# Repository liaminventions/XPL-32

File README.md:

# XPL-32

The XPL-32 is a homebrew 8-bit 6502 laptop, with four 48-pin expansion slots, and a 22-pin I/O port.
 ### XPL-32 stands for:
e**X**pandable 
**P**ersonal 
**L**aptop 
with **32**k ram
# [Blog](https://unstinkableinventions.wordpress.com/)
Here I will post hardware updates to the XPL and more.

Also, be sure to check info.txt to know if there are any issues when i code.
# Hardware Overview
## CPU
A 6502, of course. A W65C02 to be exact. 

[Datasheet](https://eater.net/datasheets/w65c02s.pdf)
## I/O
For the I/O, I've got a W65C22 VIA. Port A, Port B and the handshake bits connect to the I/O slot.
However CA2 is connected to the Video Switch Relay (VSR)
[W65C22 Datasheet](https://eater.net/datasheets/w65c22.pdf)
## Video
The XPL-32 has an expandable monochrome terminal display that uses a 6551 ACIA  at $8000 and two arduinos.
[This is the video and keyboard processer. (not made by me)](http://searle.x10host.com/MonitorKeyboard/index.html)
The video can be switched to the composite input EXTVID (on the expansion port) by toggling the VSR. (a relay that switches beetween native video and EXTVID.)

So far, for Video expansions, I've made a TMS9918a one. (the same video processer used in the TI-99/4a and the MSX)
## Sound
There is a 6581 SID at $B800 ($D400 in the c64) onboard with its potentiometer (POTX and POTY) and external sound (EXTSND) inputs on the expansion port.
I programmed support to convert most SID files, as well.
# Memory Map

# Tools I Use
## PCB Design
I currently use [EAGLE](https://www.autodesk.com/products/eagle/free-download)
## 3D Modeling
[Fusion 360](https://www.autodesk.com/products/fusion-360/overview?us_oa=dotcom-us&us_si=4e5471dc-07ed-4416-80c0-6f3e9f7c15b4&us_pt=NINVFUS&us_at=%5Bobject%20Object%5D&term=1-YEAR&tab=subscription&plc=F360)
## Coding
[VIM](https://www.vim.org/), [NVIM](https://neovim.io/)/[LunarVIM](https://www.lunarvim.org/) or [vscode](https://code.visualstudio.com/) for code editing.
[xa](https://github.com/fachat/xa65), [ca65](https://github.com/cc65/cc65) (from cc65), and [vasm](http://sun.hasenbraten.de/vasm/) for assembly.

I have "xa 6502 cross assembler" syntax highlighting in vim, and the "vasm" extension in vscode.

most source files are .s, but some are .a65 or .asm

## Debugging 

I use [Pulseview](https://sigrok.org/wiki/PulseView) with [this logic analyzer (the 2018 variant)](https://sigrok.org/wiki/Mcupro_Logic16_clone)

It was an absolute pain to set up...

Also, the SDcard-SPI decoder in libsigrokdecode was completly broken for me. (it always expected a CRC...) My fix was to make [my own custom version of the decoder](https://github.com/liaminventions/XPL-32/tree/main/debug/decoders/sdcard_spi)

The custom version is still slightly broken, but I am working on it.

I also use [decode6502 by hoglet](https://github.com/hoglet67/6502Decoder)

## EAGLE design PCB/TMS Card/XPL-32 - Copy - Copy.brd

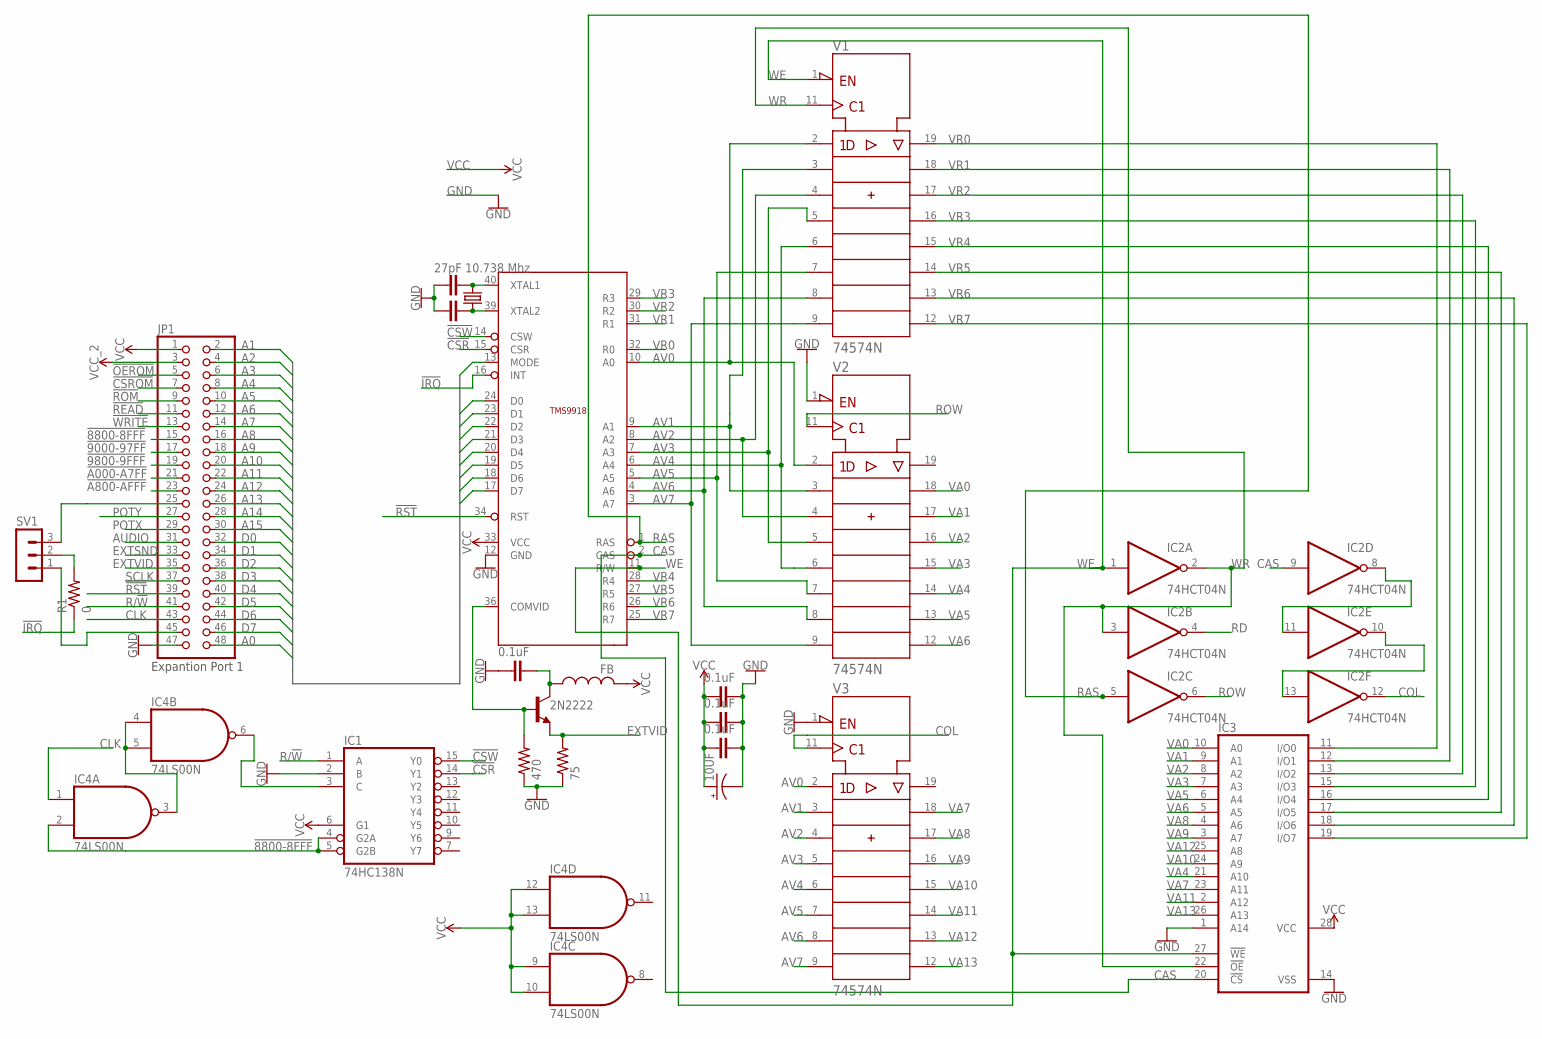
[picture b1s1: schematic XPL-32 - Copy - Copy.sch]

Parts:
10.738MHZ: CRYSTALS-NOGND-HC49; HC49
10UF: CPOL-USE2.5-7; E2,5-7
30PF, 30PF(2): C-EU025-030X050; C025-030X050
C1, C2, C3, C6: 0.1uF; C025-025X050
IC1: 74HC138N; DIL16
IC2: 74HCT04N; DIL14
IC3: 62256P; DIL28-6
IC4: 74LS00N; DIL14
JP1: PINHD-2X24/90; 2X24/90
R1: 0; 0204/7
R9: 470; 0204/7
R10: 75; 0204/7
SV1: MA03-1
T2: 2N2222; TO92-EBC-OVAL
U$4: FB
V1, V2, V3: 74574N; DIL20
VDP: TMS9918; DIP-40

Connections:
!8800-8FFF: IC1.4 (G2A), IC1.5 (G2B), IC4.2 (I1), JP1.15
!9000-97FF: JP1.17
!9800-9FFF: JP1.19
!A000-A7FF: JP1.21
!A800-AFFF: JP1.23
!CSR: IC1.14 (Y1), VDP.15 (CSR)
!CSROM: JP1.7
!CSW: IC1.15 (Y0), VDP.14 (CSW)
!IRQ: R1.1, VDP.16 (INT)
!OEROM: JP1.5
!READ: JP1.11
!ROM: JP1.9
!RST: JP1.39, VDP.34 (RST)
!WRITE: JP1.13
A0: JP1.48, VDP.13 (MODE)
A1: JP1.2
A2: JP1.4
A3: JP1.6
A4: JP1.8
A5: JP1.10
A6: JP1.12
A7: JP1.14
A8: JP1.16
A9: JP1.18
A10: JP1.20
A11: JP1.22
A12: JP1.24
A13: JP1.26
A14: JP1.28
A15: JP1.30
AUDIO: JP1.31
AV0: V1.2 (1D), V2.2 (1D), V3.2 (1D), VDP.10 (A0)
AV1: V1.3 (2D), V2.3 (2D), V3.3 (2D), VDP.9 (A1)
AV2: V1.4 (3D), V2.4 (3D), V3.4 (3D), VDP.8 (A2)
AV3: V1.5 (4D), V2.5 (4D), V3.5 (4D), VDP.7 (A3)
AV4: V1.6 (5D), V2.6 (5D), V3.6 (5D), VDP.6 (A4)
AV5: V1.7 (6D), V2.7 (6D), V3.7 (6D), VDP.5 (A5)
AV6: V1.8 (7D), V2.8 (7D), V3.8 (7D), VDP.4 (A6)
AV7: V1.9 (8D), V2.9 (8D), V3.9 (8D), VDP.3 (A7)
CAS: IC2.9 (I), IC3.20 (!CS), VDP.2 (CAS)
CLK: IC4.1 (I0), JP1.43
COL: IC2.12 (O), V3.11 (CLK)
D0: JP1.32, VDP.17 (D7)
D1: JP1.34, VDP.18 (D6)
D2: JP1.36, VDP.19 (D5)
D3: JP1.38, VDP.20 (D4)
D4: JP1.40, VDP.21 (D3)
D5: JP1.42, VDP.22 (D2)
D6: JP1.44, VDP.23 (D1)
D7: JP1.46, VDP.24 (D0)
EXTSND: JP1.33
EXTVID: JP1.35, R10.2, T2.E
GND: 10UF.-, 30PF.1, 30PF(2).1, C1.2, C2.2, C3.2, C6.1, IC1.2 (B), IC1.8 (GND), IC2.7 (GND), IC3.1 (A14), IC3.14 (VSS), IC4.7 (GND), JP1.47, R9.1, R10.1, V1.10 (-UB), V2.1 (!OC), V2.10 (-UB), V3.1 (!OC), V3.10 (-UB), VDP.12 (GND)
unnamed: IC1.3 (C), IC4.6 (O)
unnamed: JP1.45, SV1.1
unnamed: IC2.8 (O), IC2.11 (I)
unnamed: IC2.10 (O), IC2.13 (I)
unnamed: JP1.25, SV1.3
unnamed: R1.2, SV1.2
unnamed: IC4.3 (O), IC4.4 (I0), IC4.5 (I1)
unnamed: C6.2, T2.C, U$4.P$1 (1)
unnamed: R9.2, T2.B, VDP.36 (COMVID)
unnamed: 10.738MHZ.1, 30PF.2, VDP.40 (XTAL1)
unnamed: 10.738MHZ.2, 30PF(2).2, VDP.39 (XTAL2)
POTX: JP1.29
POTY: JP1.27
R/!W: IC1.1 (A), JP1.41
RAS: IC2.5 (I), VDP.1 (RAS)
RD: IC2.4 (O)
ROW: IC2.6 (O), V2.11 (CLK)
SCLK: JP1.37
VA0: IC3.10 (A0), V2.18 (2Q)
VA1: IC3.9 (A1), V2.17 (3Q)
VA2: IC3.8 (A2), V2.16 (4Q)
VA3: IC3.7 (A3), V2.15 (5Q)
VA4: IC3.21 (A10), V2.14 (6Q)
VA5: IC3.6 (A4), V2.13 (7Q)
VA6: IC3.5 (A5), V2.12 (8Q)
VA7: IC3.23 (A11), V3.18 (2Q)
VA8: IC3.4 (A6), V3.17 (3Q)
VA9: IC3.3 (A7), V3.16 (4Q)
VA10: IC3.24 (A9), V3.15 (5Q)
VA11: IC3.2 (A12), V3.14 (6Q)
VA12: IC3.25 (A8), V3.13 (7Q)
VA13: IC3.26 (A13), V3.12 (8Q)
VCC: 10UF.+, C1.1, C2.1, C3.1, IC1.6 (G1), IC1.16 (VCC), IC2.14 (VCC), IC3.28 (VCC), IC4.9 (I0), IC4.10 (I1), IC4.12 (I0), IC4.13 (I1), IC4.14 (VCC), JP1.1, U$4.P$2 (2), V1.20 (+UB), V2.20 (+UB), V3.20 (+UB), VDP.33 (VCC)
VCC_2: JP1.3
VR0: IC3.11 (I/O0), V1.19 (1Q), VDP.32 (R0)
VR1: IC3.12 (I/O1), V1.18 (2Q), VDP.31 (R1)
VR2: IC3.13 (I/O2), V1.17 (3Q), VDP.30 (R2)
VR3: IC3.15 (I/O3), V1.16 (4Q), VDP.29 (R3)
VR4: IC3.16 (I/O4), V1.15 (5Q), VDP.28 (R4)
VR5: IC3.17 (I/O5), V1.14 (6Q), VDP.27 (R5)
VR6: IC3.18 (I/O6), V1.13 (7Q), VDP.26 (R6)
VR7: IC3.19 (I/O7), V1.12 (8Q), VDP.25 (R7)
WE: IC2.1 (I), IC3.27 (!WE), V1.1 (!OC), VDP.11 (R/W)
WR: IC2.2 (O), IC2.3 (I), IC3.22 (!OE), V1.11 (CLK)

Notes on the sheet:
Expantion Port 1
27pF 10.738 Mhz

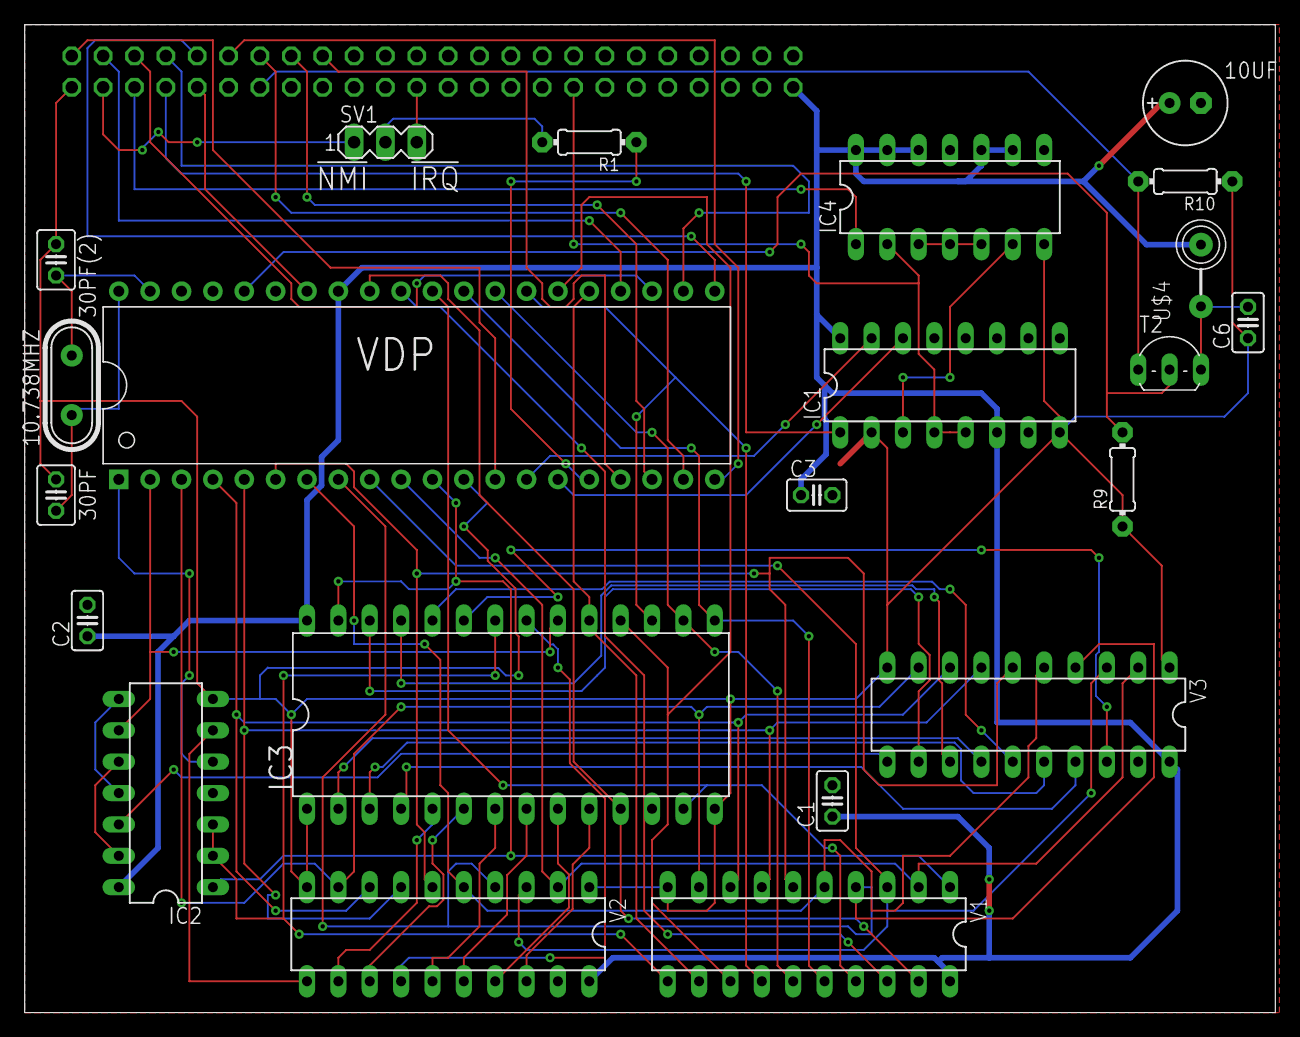
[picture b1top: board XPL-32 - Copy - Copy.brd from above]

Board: 2 copper layers, 101.3 x 80.0 mm, 23 parts (1 on the bottom side), 66 nets.

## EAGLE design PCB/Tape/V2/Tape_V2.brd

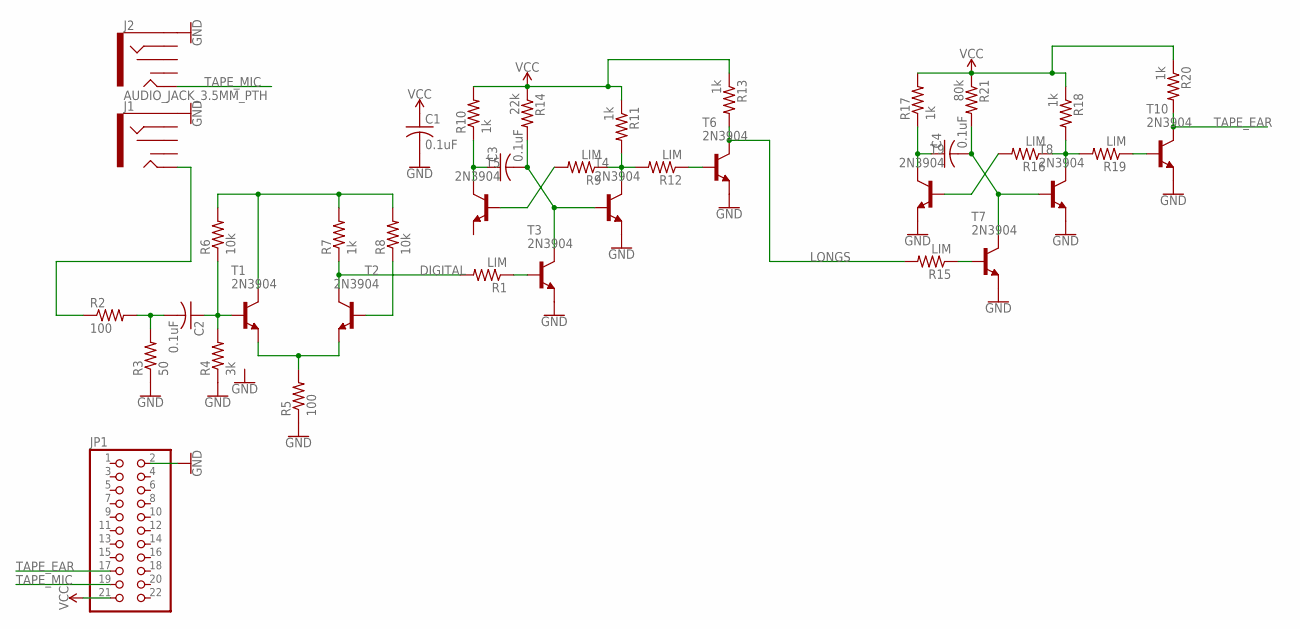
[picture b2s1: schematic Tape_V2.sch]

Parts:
C1, C2, C3, C4: 0.1uF; C025-030X050
J1, J2: AUDIO_JACK_3.5MM_PTH; AUDIO-JACK
JP1: PINHD-2X11/90; 2X11/90
R1, R9, R12, R15, R16, R19: LIM; 0204/7
R2, R5: 100; 0204/7
R3: 50; 0204/7
R4: 3k; 0204/7
R6, R8: 10k; 0204/7
R7, R10, R11, R13, R17, R18, R20: 1k; 0204/7
R14: 22k; 0204/7
R21: 80k; 0204/7
T1, T2, T3, T4, T5, T6, T7, T8, T9, T10: 2N3904; TO92

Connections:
DIGITAL: R1.2, R7.1, T2.1 (C)
GND: C1.2, J1.SLEEVE, J2.SLEEVE, JP1.2, R3.1, R4.1, R5.1, T3.3 (E), T4.3 (E), T6.3 (E), T7.3 (E), T8.3 (E), T9.3 (E), T10.3 (E); also elsewhere on the board
LONGS: R13.2, R15.2, T6.1 (C)
unnamed: R5.2, T1.3 (E), T2.3 (E)
unnamed: C2.1, R4.2, R6.1, T1.2 (B)
unnamed: C2.2, R2.2, R3.2
unnamed: R6.2, R7.2, R8.2, T1.1 (C)
unnamed: R1.1, T3.2 (B)
unnamed 8: R8.1, T2.2 (B); also elsewhere on the board
unnamed: J1.TIP, R2.1
unnamed: C3.2, R14.2, T3.1 (C), T4.2 (B)
unnamed: R9.2, T5.2 (B)
unnamed: C3.1, R10.1, T5.1 (C)
unnamed: R9.1, R11.2, R12.2, T4.1 (C)
unnamed: R12.1, T6.2 (B)
unnamed: R15.1, T7.2 (B)
unnamed: C4.2, R21.2, T7.1 (C), T8.2 (B)
unnamed: R16.2, T9.2 (B)
unnamed: C4.1, R17.1, T9.1 (C)
unnamed: R16.1, R18.2, R19.2, T8.1 (C)
unnamed: R19.1, T10.2 (B)
TAPE_EAR: JP1.17, R20.2, T10.1 (C)
TAPE_MIC: J2.TIP, JP1.19
VCC: C1.1, JP1.21, R10.2, R11.1, R13.1, R14.1, R17.2, R18.1, R20.1, R21.1

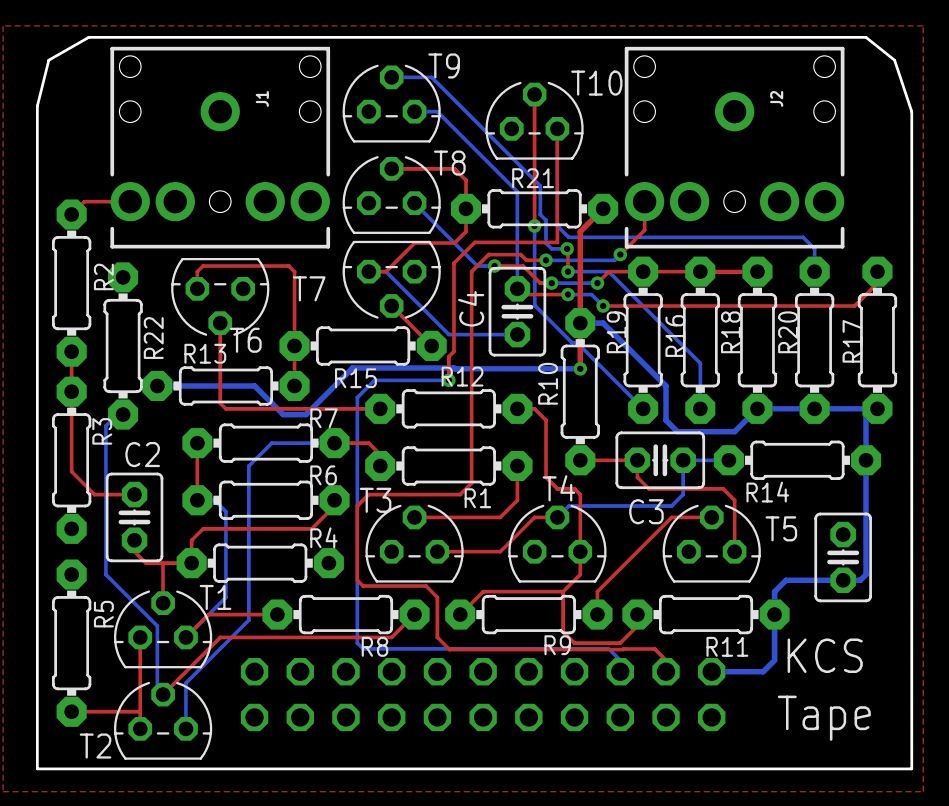
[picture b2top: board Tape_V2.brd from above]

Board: 2 copper layers, 48.6 x 40.6 mm, 39 parts (1 on the bottom side), 24 nets.

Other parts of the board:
R22: 3k; 0204/7

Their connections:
GND: R22.1; also elsewhere on the board
unnamed 8: R22.2; also elsewhere on the board

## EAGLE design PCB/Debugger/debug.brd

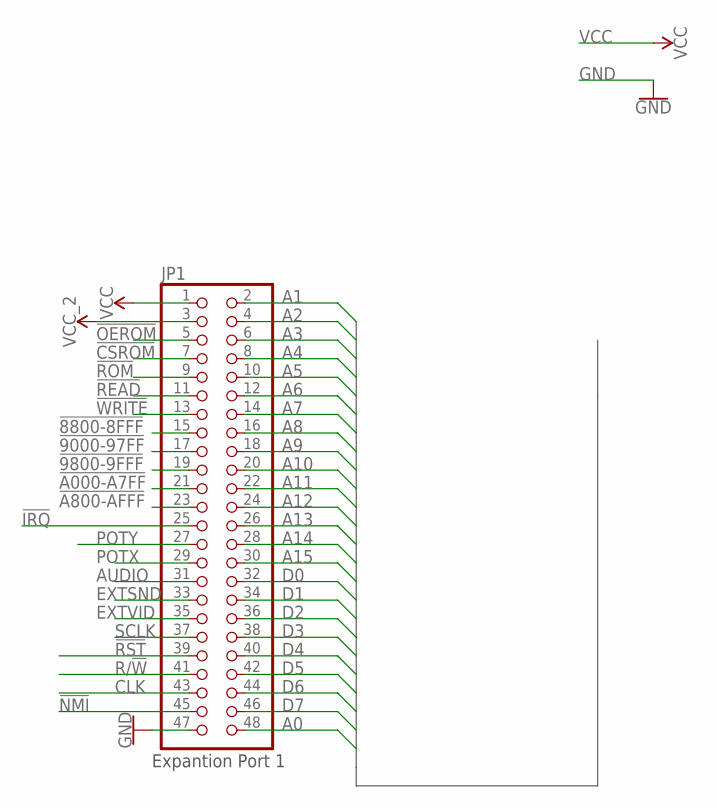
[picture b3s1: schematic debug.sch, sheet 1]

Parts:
JP1: PINHD-2X24/90; 2X24/90

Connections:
!8800-8FFF: JP1.15
!9000-97FF: JP1.17
!9800-9FFF: JP1.19
!A000-A7FF: JP1.21
!A800-AFFF: JP1.23
!CSROM: JP1.7
!IRQ: JP1.25; also elsewhere on the board
!NMI: JP1.45; also elsewhere on the board
!OEROM: JP1.5
!READ: JP1.11
!ROM: JP1.9
!RST: JP1.39
!WRITE: JP1.13
A0: JP1.48; also elsewhere on the board
A1: JP1.2; also elsewhere on the board
A2: JP1.4; also elsewhere on the board
A3: JP1.6; also elsewhere on the board
A4: JP1.8; also elsewhere on the board
A5: JP1.10; also elsewhere on the board
A6: JP1.12; also elsewhere on the board
A7: JP1.14; also elsewhere on the board
A8: JP1.16; also elsewhere on the board
A9: JP1.18; also elsewhere on the board
A10: JP1.20; also elsewhere on the board
A11: JP1.22; also elsewhere on the board
A12: JP1.24; also elsewhere on the board
A13: JP1.26; also elsewhere on the board
A14: JP1.28; also elsewhere on the board
A15: JP1.30; also elsewhere on the board
AUDIO: JP1.31
CLK: JP1.43; also elsewhere on the board
D0: JP1.32; also elsewhere on the board
D1: JP1.34; also elsewhere on the board
D2: JP1.36; also elsewhere on the board
D3: JP1.38; also elsewhere on the board
D4: JP1.40; also elsewhere on the board
D5: JP1.42; also elsewhere on the board
D6: JP1.44; also elsewhere on the board
D7: JP1.46; also elsewhere on the board
EXTSND: JP1.33
EXTVID: JP1.35
GND: JP1.47; also elsewhere on the board
POTX: JP1.29
POTY: JP1.27
R/!W: JP1.41; also elsewhere on the board
SCLK: JP1.37
VCC: JP1.1; also elsewhere on the board
VCC_2: JP1.3

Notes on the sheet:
Expantion Port 1

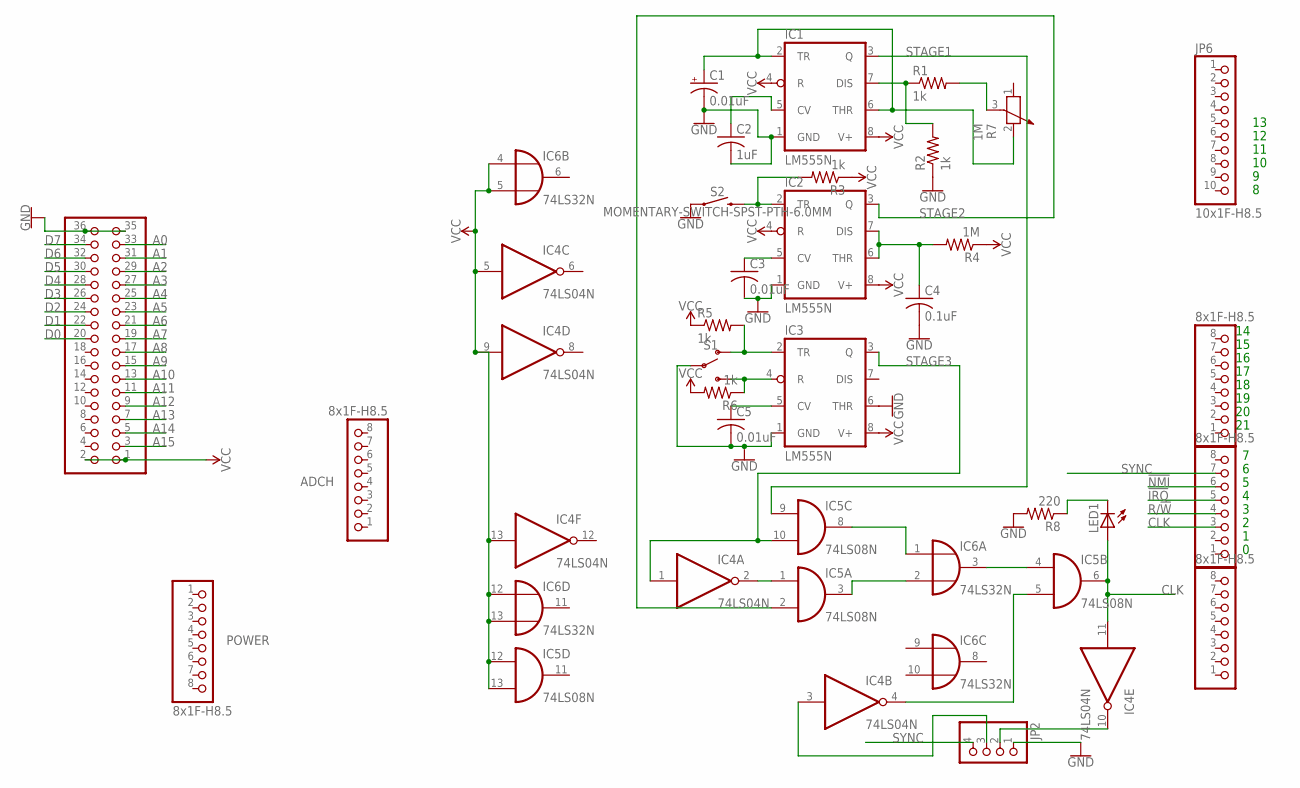
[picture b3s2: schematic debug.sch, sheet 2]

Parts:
ADCH: 8x1F-H8.5; 1X08
ADCL: 8x1F-H8.5; 1X08
C1: 0.01uF; E5-10,5
C2: 1uF; C025-030X050
C3, C5: 0.01uF; C025-030X050
C4: 0.1uF; C025-030X050
COMMUNICATION: 8x1F-H8.5; 1X08
IC1, IC2, IC3: LM555N; DIL08-ROUND
IC4: 74LS04N; DIL14
IC5: 74LS08N; DIL14
IC6: 74LS32N; DIL14
JP2: PINHD-1X4; 1X04
JP6: 10x1F-H8.5; 1X10
LED1: LED5MM
POWER: 8x1F-H8.5; 1X08
PWML: 8x1F-H8.5; 1X08
R1, R2, R3, R5, R6: 1k; 0204/7
R4: 1M; 0204/7
R7: 1M; PT-10
R8: 220; 0204/7
S1: SWITCH-SPDT-PTH-11.6X4.0MM-LOCK; SWITCH_SPDT_PTH_11.6X4.0MM_LOCK
S2: MOMENTARY-SWITCH-SPST-PTH-6.0MM; TACTILE_SWITCH_PTH_6.0MM
XIO: 18x2F-H8.5; 2X18

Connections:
!IRQ: PWML.5; also elsewhere on the board
!NMI: PWML.6; also elsewhere on the board
A0: XIO.33; also elsewhere on the board
A1: XIO.31; also elsewhere on the board
A2: XIO.29; also elsewhere on the board
A3: XIO.27; also elsewhere on the board
A4: XIO.25; also elsewhere on the board
A5: XIO.23; also elsewhere on the board
A6: XIO.21; also elsewhere on the board
A7: XIO.19; also elsewhere on the board
A8: XIO.17; also elsewhere on the board
A9: XIO.15; also elsewhere on the board
A10: XIO.13; also elsewhere on the board
A11: XIO.11; also elsewhere on the board
A12: XIO.9; also elsewhere on the board
A13: XIO.7; also elsewhere on the board
A14: XIO.5; also elsewhere on the board
A15: XIO.3; also elsewhere on the board
CLK: IC4.11 (I), IC5.6 (O), LED1.A, PWML.3; also elsewhere on the board
D0: XIO.20; also elsewhere on the board
D1: XIO.22; also elsewhere on the board
D2: XIO.24; also elsewhere on the board
D3: XIO.26; also elsewhere on the board
D4: XIO.28; also elsewhere on the board
D5: XIO.30; also elsewhere on the board
D6: XIO.32; also elsewhere on the board
D7: XIO.34; also elsewhere on the board
GND: C1.-, C2.2, C3.2, C4.2, C5.2, IC1.1 (GND), IC2.1 (GND), IC3.1 (GND), IC3.6 (THR), IC4.7 (GND), IC5.7 (GND), IC6.7 (GND), JP2.1, R2.1, R8.2, S1.2, S2.1, XIO.35, XIO.36; also elsewhere on the board
unnamed: C1.+, IC1.2 (TR), IC1.6 (THR), R7.2
unnamed: C2.1, IC1.5 (CV)
unnamed: IC2.2 (TR), R3.2, S2.3 (2)
unnamed: IC1.7 (DIS), R1.1, R2.2
unnamed: R1.2, R7.3
unnamed: C4.1, IC2.6 (THR), IC2.7 (DIS), R4.2
unnamed: C3.1, IC2.5 (CV)
unnamed: C5.1, IC3.5 (CV)
unnamed: IC3.2 (TR), R5.2, S1.1 (O)
unnamed: IC3.4 (R), R6.1, S1.3 (S)
unnamed: IC4.2 (O), IC5.1 (I0)
unnamed: IC5.8 (O), IC6.1 (I0)
unnamed: IC5.3 (O), IC6.2 (I1)
unnamed: IC5.4 (I0), IC6.3 (O)
unnamed: IC4.4 (O), IC5.5 (I1)
unnamed: IC4.3 (I), JP2.3
unnamed: IC4.10 (O), JP2.2
unnamed: LED1.K (C), R8.1
R/!W: PWML.4; also elsewhere on the board
STAGE1: IC1.3 (Q), IC5.9 (I0)
STAGE2: IC2.3 (Q), IC5.2 (I1)
STAGE3: IC3.3 (Q), IC4.1 (I), IC5.10 (I1)
SYNC: JP2.4, PWML.7
VCC: IC1.4 (R), IC1.8 (V+), IC2.4 (R), IC2.8 (V+), IC3.8 (V+), IC4.5 (I), IC4.9 (I), IC4.13 (I), IC4.14 (VCC), IC5.12 (I0), IC5.13 (I1), IC5.14 (VCC), IC6.4 (I0), IC6.5 (I1), IC6.12 (I0), IC6.13 (I1), IC6.14 (VCC), R3.1, R4.1, R5.1, R6.2, XIO.1, XIO.2; also elsewhere on the board

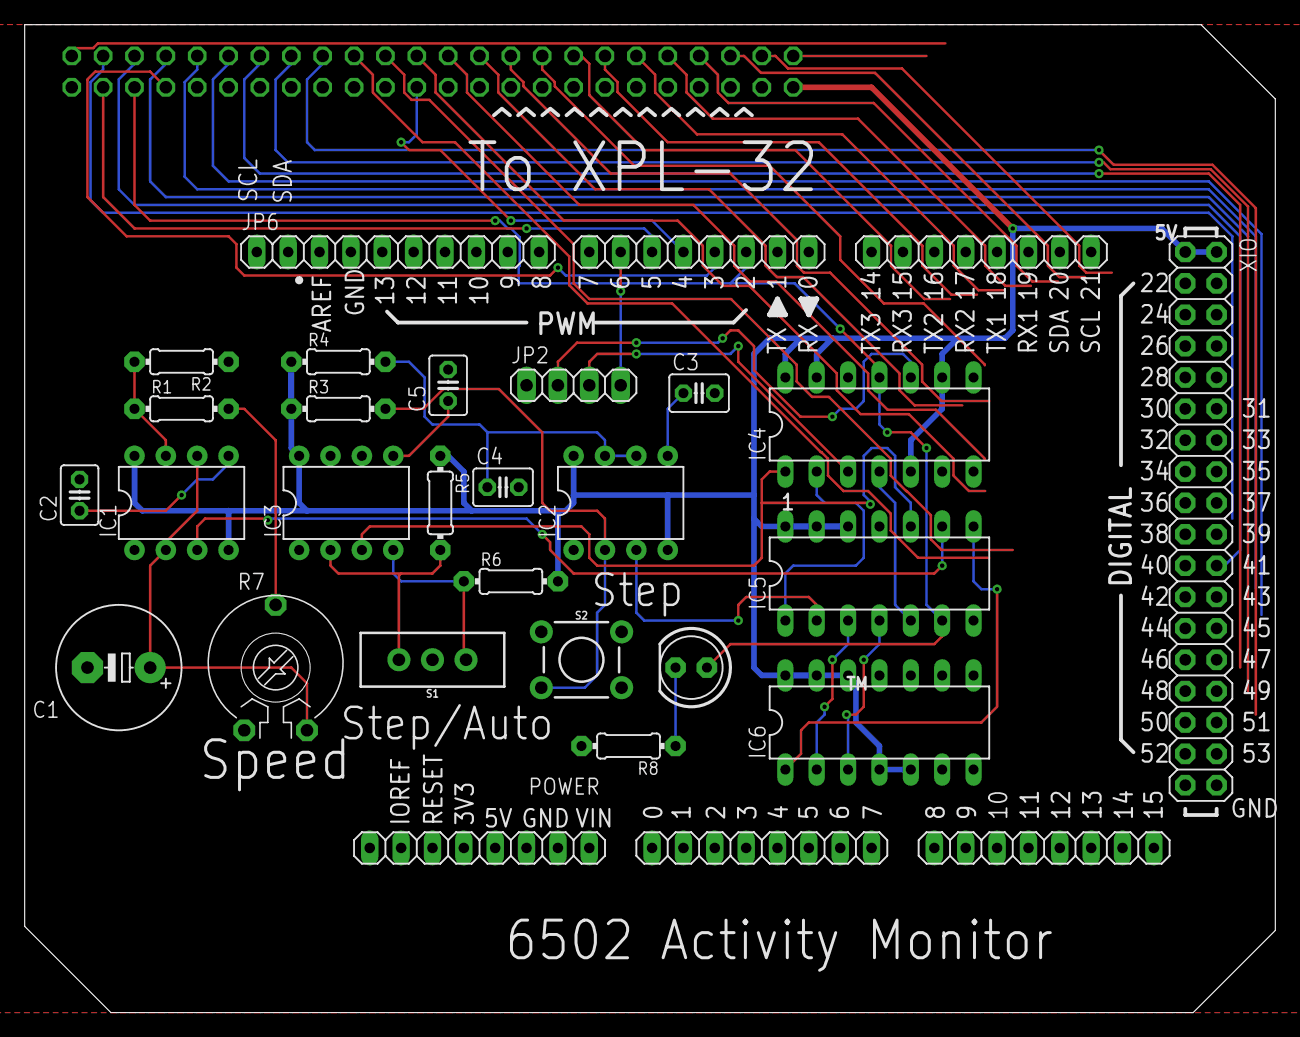
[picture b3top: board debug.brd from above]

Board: 2 copper layers, 101.3 x 80.0 mm, 31 parts (1 on the bottom side), 52 nets.

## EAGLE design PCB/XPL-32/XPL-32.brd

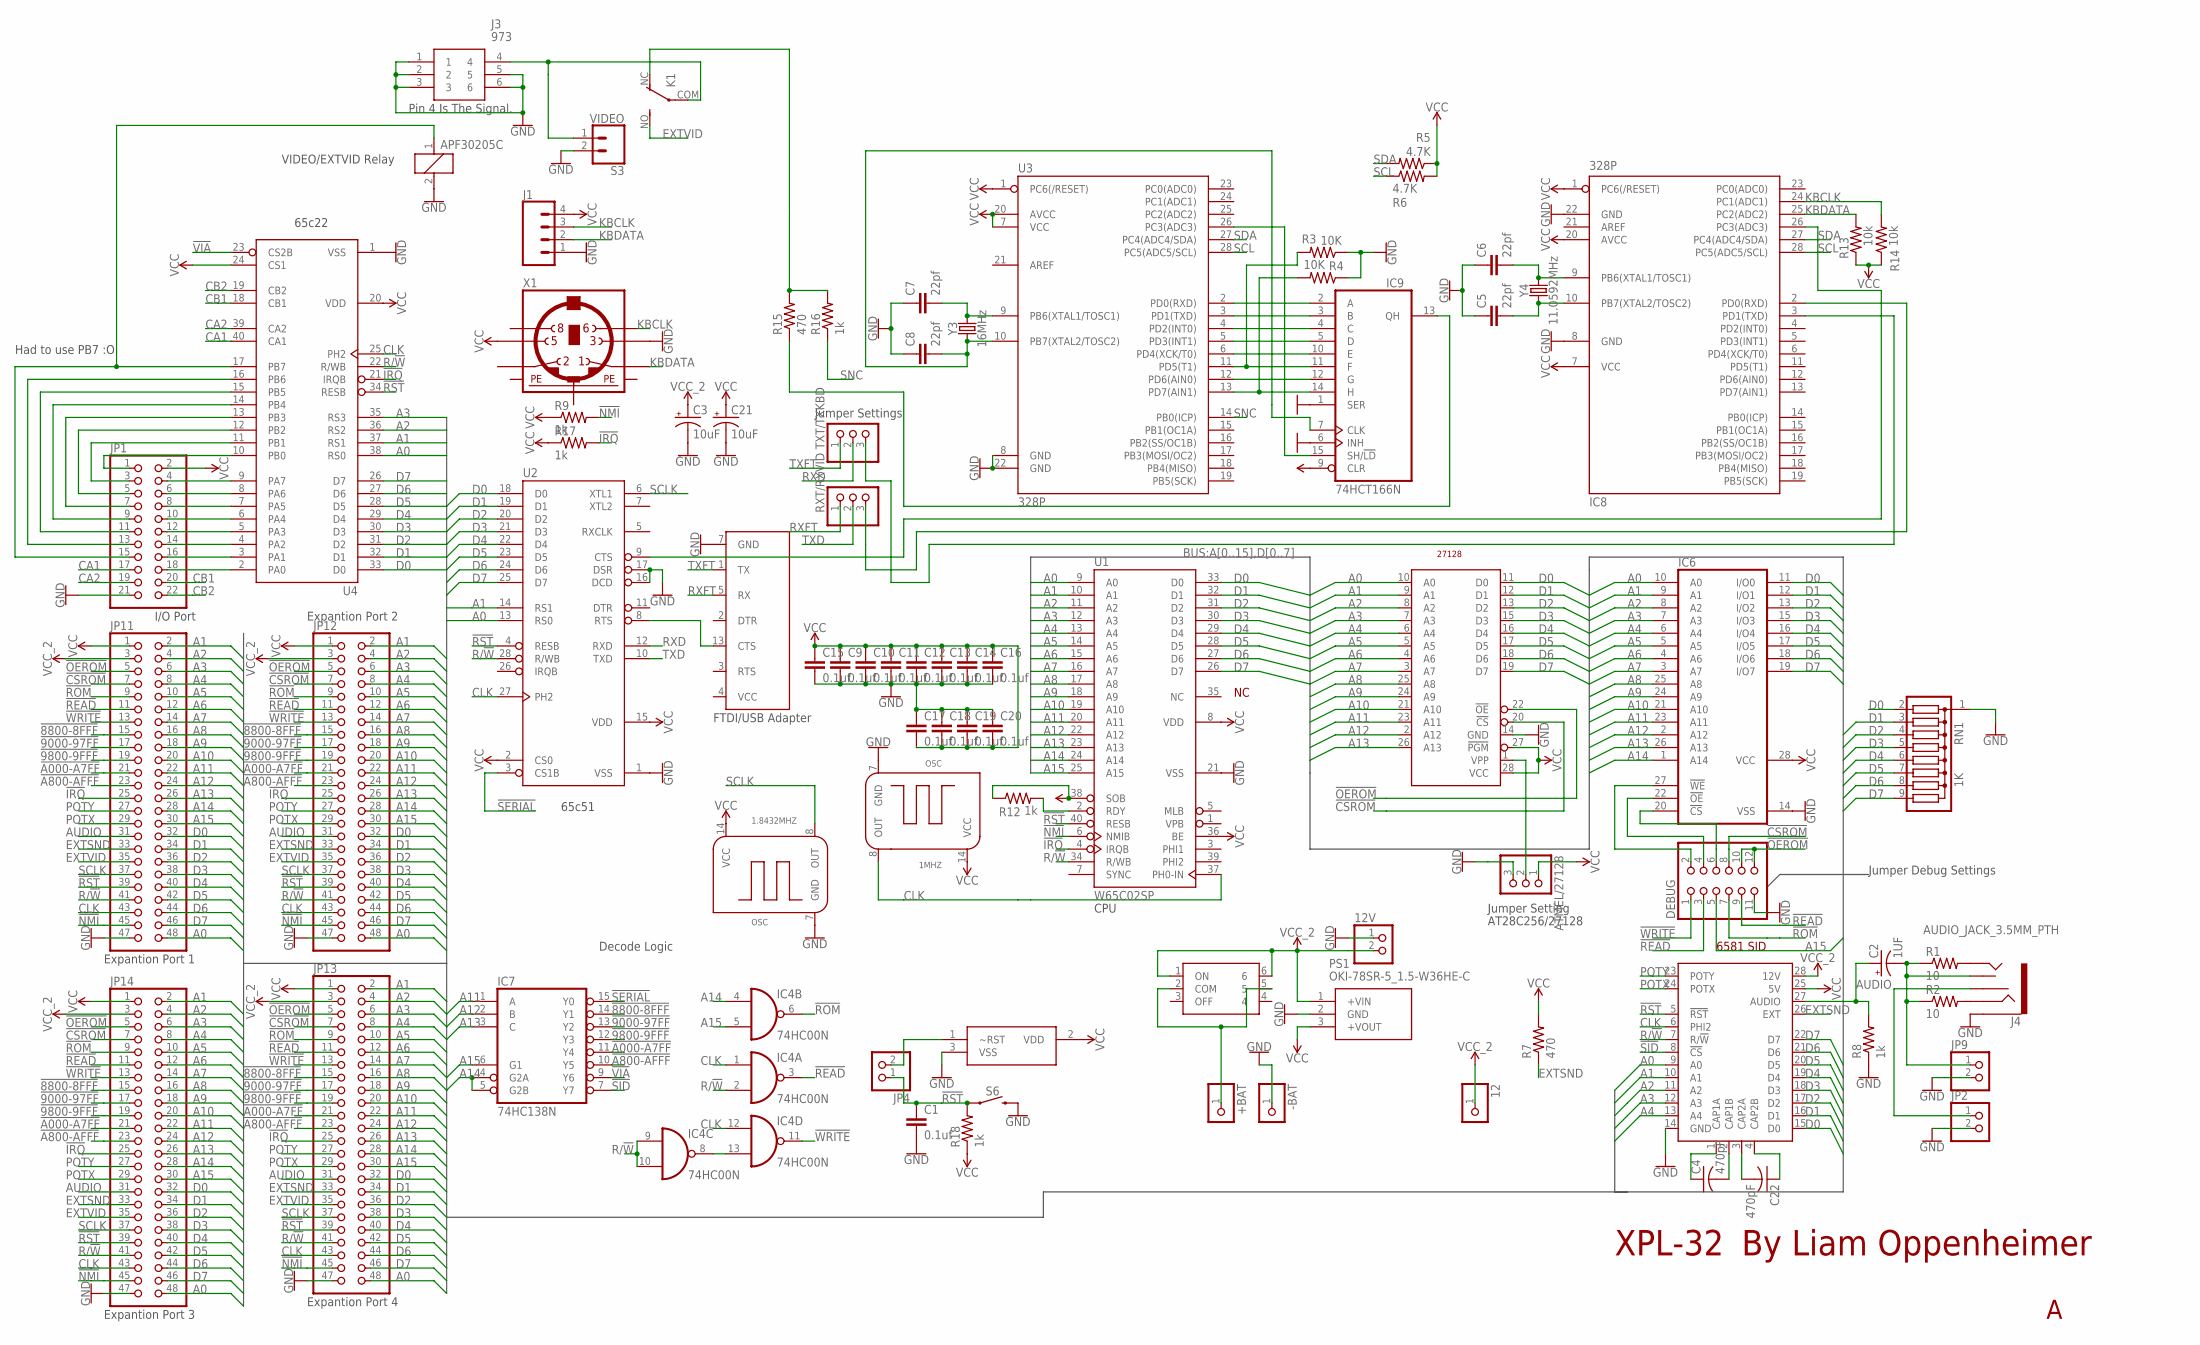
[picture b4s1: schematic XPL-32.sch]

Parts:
1.8432MHZ, 1MHZ: OSC; OSCCAN
12: PINHD-1X1; 1X01
12V: PINHD-1X2; 1X02
+BAT: PINHD-1X1; 1X01
-BAT: PINHD-1X1; 1X01
ATMEL/27128: PINHD-1X3; 1X03
C1, C9, C10, C11, C12, C13, C14, C15, C16, C17, C18, C19, C20: 0.1uf; C025-025X050
C2: 1UF; E2,5-7
C3, C21: 10uF; E2,5-7
C4, C22: 470pF; C150-054X183
C5, C6, C7, C8: 22pf; C025-025X050
DEBUG: PINHD-2X6; 2X06
IC4: 74HC00N; DIL14
IC6: 62256P; DIL28-6
IC7: 74HC138N; DIL16
IC8: 328P; DIL28-3
IC9: 74HCT166N; DIL16
IC10: MCP120-450DI_TO; TO127P254X495-3
J1: CONN_041X04_NO_SILK; 1X04_NO_SILK
J3: 973
J4: AUDIO_JACK_3.5MM_PTH; AUDIO-JACK
JP1: PINHD-2X11/90; 2X11/90
JP2, JP4, JP9: PINHD-1X2; 1X02
JP11, JP12, JP13, JP14: PINHD-2X24/90; 2X24/90
K1: APF30205C; APF30212C
PS1: OKI-78SR-5_1.5-W36HE-C; OKI78SR515W36HEC
R1, R2: 10; 0204/7
R3, R4: 10K; 0204/7
R5, R6: 4.7K; 0204/7
R7, R15: 470; 0204/7
R8, R9, R12, R16, R17, R18: 1k; 0204/7
R13, R14: 10k; 0204/7
RN1: 1K; SIL9
RXT/RXVID: PINHD-1X3; 1X03
S3: VIDEO; 1X02_NO_SILK
S6: MOMENTARY-SWITCH-SPST-PTH-6.0MM; TACTILE_SWITCH_PTH_6.0MM
TXT/TXKBD: PINHD-1X3; 1X03
U1: W65C02SP; DIP-40
U2: G65SC51P; DIP-28
U3: 328P; DIP28
U4: G65SC22P; DIP-40
U6: FTDI
U7: AT28C256/27128; DIP-28
U$1: TOGGLE_PUSHBUTTON; TOGGLE_BUTTON
U$2: 6581; DIP-28
X1: MINI_DIN_6; M_DIN6
Y3: 16MHz; HC49U
Y4: 11.0592MHz; HC49U

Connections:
!8800-8FFF: IC7.14 (Y1), JP11.15, JP12.15, JP13.15, JP14.15
!9000-97FF: IC7.13 (Y2), JP11.17, JP12.17, JP13.17, JP14.17
!9800-9FFF: IC7.12 (Y3), JP11.19, JP12.19, JP13.19, JP14.19
!A000-A7FF: IC7.11 (Y4), JP11.21, JP12.21, JP13.21, JP14.21
!A800-AFFF: IC7.10 (Y5), JP11.23, JP12.23, JP13.23, JP14.23
!CSROM: DEBUG.8, JP11.7, JP12.7, JP13.7, JP14.7, U7.20 (!CS)
!IRQ: JP11.25, JP12.25, JP13.25, JP14.25, R17.2, U1.4 (IRQB), U4.21 (IRQB)
!NMI: JP11.45, JP12.45, JP13.45, JP14.45, R9.2, U1.6 (NMIB)
!OEROM: DEBUG.10, DEBUG.12, JP11.5, JP12.5, JP13.5, JP14.5, U7.22 (!OE)
!READ: DEBUG.3, DEBUG.9, IC4.3 (O), JP11.11, JP12.11, JP13.11, JP14.11
!ROM: DEBUG.7, IC4.6 (O), JP11.9, JP12.9, JP13.9, JP14.9
!RST: C1.1, JP4.1, JP11.39, JP12.39, JP13.39, JP14.39, R18.2, S6.1, U1.40 (RESB), U2.4 (RESB), U4.34 (RESB), U$2.5 (!RST)
!SERIAL: IC7.15 (Y0), U2.3 (CS1B)
!SID: IC7.7 (Y7), U$2.8 (!CS)
!VIA: IC7.9 (Y6), U4.23 (CS2B)
!WRITE: DEBUG.1, IC4.11 (O), JP11.13, JP12.13, JP13.13, JP14.13
A0: IC6.10 (A0), JP11.48, JP12.48, JP13.48, JP14.48, U1.9 (A0), U2.13 (RS0), U4.38 (RS0), U7.10 (A0), U$2.9 (A0)
A1: IC6.9 (A1), JP11.2, JP12.2, JP13.2, JP14.2, U1.10 (A1), U2.14 (RS1), U4.37 (RS1), U7.9 (A1), U$2.10 (A1)
A2: IC6.8 (A2), JP11.4, JP12.4, JP13.4, JP14.4, U1.11 (A2), U4.36 (RS2), U7.8 (A2), U$2.11 (A2)
A3: IC6.7 (A3), JP11.6, JP12.6, JP13.6, JP14.6, U1.12 (A3), U4.35 (RS3), U7.7 (A3), U$2.12 (A3)
A4: IC6.6 (A4), JP11.8, JP12.8, JP13.8, JP14.8, U1.13 (A4), U7.6 (A4), U$2.13 (A4)
A5: IC6.5 (A5), JP11.10, JP12.10, JP13.10, JP14.10, U1.14 (A5), U7.5 (A5)
A6: IC6.4 (A6), JP11.12, JP12.12, JP13.12, JP14.12, U1.15 (A6), U7.4 (A6)
A7: IC6.3 (A7), JP11.14, JP12.14, JP13.14, JP14.14, U1.16 (A7), U7.3 (A7)
A8: IC6.25 (A8), JP11.16, JP12.16, JP13.16, JP14.16, U1.17 (A8), U7.25 (A8)
A9: IC6.24 (A9), JP11.18, JP12.18, JP13.18, JP14.18, U1.18 (A9), U7.24 (A9)
A10: IC6.21 (A10), JP11.20, JP12.20, JP13.20, JP14.20, U1.19 (A10), U7.21 (A10)
A11: IC6.23 (A11), IC7.1 (A), JP11.22, JP12.22, JP13.22, JP14.22, U1.20 (A11), U7.23 (A11)
A12: IC6.2 (A12), IC7.2 (B), JP11.24, JP12.24, JP13.24, JP14.24, U1.22 (A12), U7.2 (A12)
A13: IC6.26 (A13), IC7.3 (C), JP11.26, JP12.26, JP13.26, JP14.26, U1.23 (A13), U7.26 (A13)
A14: IC4.4 (I0), IC6.1 (A14), IC7.4 (G2A), IC7.5 (G2B), JP11.28, JP12.28, JP13.28, JP14.28, U1.24 (A14)
A15: DEBUG.5, IC4.5 (I1), IC7.6 (G1), JP11.30, JP12.30, JP13.30, JP14.30, U1.25 (A15)
AUDIO: C2.+, JP11.31, JP12.31, JP13.31, JP14.31, R8.2, U$2.27 (AUDIO)
CA1: JP1.17, U4.40 (CA1)
CA2: JP1.19, U4.39 (CA2)
CB1: JP1.20, U4.18 (CB1)
CB2: JP1.22, U4.19 (CB2)
CLK: 1MHZ.8 (OUT), IC4.1 (I0), IC4.12 (I0), JP11.43, JP12.43, JP13.43, JP14.43, U1.37 (PH0-IN), U2.27 (PH2), U4.25 (PH2), U$2.6 (PHI2)
D0: IC6.11 (I/O0), JP11.32, JP12.32, JP13.32, JP14.32, RN1.2, U1.33 (D0), U2.18 (D0), U4.33 (D0), U7.11 (D0), U$2.15 (D0)
D1: IC6.12 (I/O1), JP11.34, JP12.34, JP13.34, JP14.34, RN1.3, U1.32 (D1), U2.19 (D1), U4.32 (D1), U7.12 (D1), U$2.16 (D1)
D2: IC6.13 (I/O2), JP11.36, JP12.36, JP13.36, JP14.36, RN1.4, U1.31 (D2), U2.20 (D2), U4.31 (D2), U7.13 (D2), U$2.17 (D2)
D3: IC6.15 (I/O3), JP11.38, JP12.38, JP13.38, JP14.38, RN1.5, U1.30 (D3), U2.21 (D3), U4.30 (D3), U7.15 (D3), U$2.18 (D3)
D4: IC6.16 (I/O4), JP11.40, JP12.40, JP13.40, JP14.40, RN1.6, U1.29 (D4), U2.22 (D4), U4.29 (D4), U7.16 (D4), U$2.19 (D4)
D5: IC6.17 (I/O5), JP11.42, JP12.42, JP13.42, JP14.42, RN1.7, U1.28 (D5), U2.23 (D5), U4.28 (D5), U7.17 (D5), U$2.20 (D5)
D6: IC6.18 (I/O6), JP11.44, JP12.44, JP13.44, JP14.44, RN1.8, U1.27 (D6), U2.24 (D6), U4.27 (D6), U7.18 (D6), U$2.21 (D6)
D7: IC6.19 (I/O7), JP11.46, JP12.46, JP13.46, JP14.46, RN1.9, U1.26 (D7), U2.25 (D7), U4.26 (D7), U7.19 (D7), U$2.22 (D7)
EXTSND: JP11.33, JP12.33, JP13.33, JP14.33, R7.1, U$2.26 (EXT)
EXTVID: JP11.35, JP12.35, JP13.35, JP14.35, K1.NO (S)
GND: 1.8432MHZ.7 (GND), 1MHZ.7 (GND), 12V.1, -BAT.1, ATMEL/27128.3, C1.2, C3.-, C5.1, C6.1, C7.1, C8.1, C9.2, C10.2, C11.2, C12.2, C13.2, C14.2, C15.2, C16.2, C17.1, C18.1, C19.1, C20.1, C21.-, DEBUG.11, IC4.7 (GND), IC6.14 (VSS), IC7.8 (GND), IC8.8 (GND), IC8.22 (GND), IC9.1 (SER), IC9.6 (INH), IC9.8 (GND), IC10.3 (VSS), J1.1, J3.1, J3.2, J3.3, J3.5, J3.6, J4.SLEEVE, JP1.21, JP2.2, JP9.2, JP11.47, JP12.47, JP13.47, JP14.47, K1.2, PS1.2 (GND), R3.1, R4.1, R8.1, RN1.1, S3.2, S6.3 (2), U1.21 (VSS), U2.1 (VSS), U2.16 (DCD), U2.17 (DSR), U3.8 (GND), U3.22 (GND), U4.1 (VSS), U6.7 (GND), U7.14 (GND), U$2.14 (GND), X1.3
KBCLK: IC8.24 (PC1(ADC1)), J1.3, R14.2, X1.6
KBDATA: IC8.25 (PC2(ADC2)), J1.2, R13.2, X1.1
unnamed: ATMEL/27128.2, U7.1 (VPP)
unnamed: IC10.1 (~RST), JP4.2
unnamed: J4.RSH, JP2.1
unnamed: J4.TIP, R1.2
unnamed: +BAT.1, U$1.2 (COM), U$1.5
unnamed: J4.RING, R2.2
unnamed: IC4.8 (O), IC4.13 (I1)
unnamed: JP1.1, U4.10 (PB0)
unnamed: DEBUG.2, IC6.27 (!WE)
unnamed: IC8.2 (PD0(RXD)), RXT/RXVID.3
unnamed: IC8.3 (PD1(TXD)), TXT/TXKBD.3
unnamed: JP1.3, U4.11 (PB1)
unnamed: C2.-, J4.TSH, JP9.1, R1.1, R2.1
unnamed: JP1.5, U4.12 (PB2)
unnamed: JP1.15, K1.1, U4.17 (PB7)
unnamed: C22.2, U$2.3 (CAP2A)
unnamed: C4.2, U$2.2 (CAP1B)
unnamed: C22.1, U$2.4 (CAP2B)
unnamed: JP1.7, U4.13 (PB3)
unnamed: JP1.9, U4.14 (PB4)
unnamed: R12.2, U1.2 (RDY)
unnamed: C4.1, U$2.1 (CAP1A)
unnamed: U2.8 (RTS), U6.13 (CTS)
unnamed: JP1.11, U4.15 (PB5)
unnamed: C6.2, IC8.9 (PB6(XTAL1/TOSC1)), Y4.2
unnamed: C5.2, IC8.10 (PB7(XTAL2/TOSC2)), Y4.1
unnamed: C7.2, U3.9 (PB6(XTAL1/TOSC1)), Y3.2
unnamed: C8.2, IC9.7 (CLK), U3.10 (PB7(XTAL2/TOSC2)), Y3.1
unnamed: IC8.26 (PC3(ADC3)), U2.9 (CTS)
unnamed: IC9.15 (SH/!LD), U3.26 (PC3(ADC3))
unnamed: J3.4, K1.COM, S3.1
unnamed: JP1.13, U4.16 (PB6)
unnamed: K1.NC (O), R15.2, R16.2
unnamed: JP1.18, U4.2 (PA0)
unnamed: JP1.16, U4.3 (PA1)
unnamed: JP1.14, U4.4 (PA2)
unnamed: JP1.12, U4.5 (PA3)
unnamed: JP1.10, U4.6 (PA4)
unnamed: JP1.8, U4.7 (PA5)
unnamed: JP1.6, U4.8 (PA6)
unnamed: JP1.4, U4.9 (PA7)
unnamed: IC9.2 (A), U3.2 (PD0(RXD))
unnamed: IC9.3 (B), U3.3 (PD1(TXD))
unnamed: IC9.4 (C), U3.4 (PD2(INT0))
unnamed: IC9.5 (D), U3.5 (PD3(INT1))
unnamed: IC9.10 (E), U3.6 (PD4(XCK/T0))
unnamed: IC9.11 (F), R3.2, U3.11 (PD5(T1))
unnamed: IC9.12 (G), U3.12 (PD6(AIN0))
unnamed: IC9.14 (H), R4.2, U3.13 (PD7(AIN1))
unnamed: IC9.13 (QH), R15.1
unnamed: DEBUG.4, IC6.22 (!OE)
unnamed: DEBUG.6, IC6.20 (!CS)
PE1: X1.SH1 (PE1)
PE2: X1.SH2 (PE2)
PE3: X1.SH3 (PE3)
POTX: JP11.29, JP12.29, JP13.29, JP14.29, U$2.24 (POTX)
POTY: JP11.27, JP12.27, JP13.27, JP14.27, U$2.23 (POTY)
R/!W: IC4.2 (I1), IC4.9 (I0), IC4.10 (I1), JP11.41, JP12.41, JP13.41, JP14.41, U1.34 (R/WB), U2.28 (R/WB), U4.22 (R/WB), U$2.7 (R/!W)
RXD: TXT/TXKBD.2, U2.12 (RXD)
RXFT: RXT/RXVID.1, U6.5 (RX)
SCL: IC8.28 (PC5(ADC5/SCL)), R6.1, U3.28 (PC5(ADC5/SCL))
SCLK: 1.8432MHZ.8 (OUT), JP11.37, JP12.37, JP13.37, JP14.37, U2.6 (XTL1)
SDA: IC8.27 (PC4(ADC4/SDA)), R5.2, U3.27 (PC4(ADC4/SDA))
SNC: R16.1, U3.14 (PB0(ICP))
TXD: RXT/RXVID.2, U2.10 (TXD)
TXFT: TXT/TXKBD.1, U6.1 (TX)
VCC: 1.8432MHZ.14 (VCC), 1MHZ.14 (VCC), ATMEL/27128.1, C9.1, C10.1, C11.1, C12.1, C13.1, C14.1, C15.1, C16.1, C17.2, C18.2, C19.2, C20.2, C21.+, IC4.14 (VCC), IC6.28 (VCC), IC7.16 (VCC), IC8.1 (PC6(/RESET)), IC8.7 (VCC), IC8.20 (AVCC), IC9.9 (CLR), IC9.16 (VCC), IC10.2 (VDD), J1.4, JP1.2, JP11.1, JP12.1, JP13.1, JP14.1, PS1.3 (+VOUT), R5.1, R6.2, R7.2, R9.1, R12.1, R13.1, R14.1, R17.1, R18.1, U1.8 (VDD), U1.36 (BE), U1.38 (SOB), U2.2 (CS0), U2.15 (VDD), U3.1 (PC6(/RESET)), U3.7 (VCC), U3.20 (AVCC), U4.20 (VDD), U4.24 (CS1), U7.27 (!PGM), U7.28 (VCC), U$2.25 (5V), X1.5
VCC_2: 12.1, 12V.2, C3.+, JP11.3, JP12.3, JP13.3, JP14.3, PS1.1 (+VIN), U$1.1 (ON), U$1.6, U$2.28 (12V)

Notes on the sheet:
XPL-32
By Liam Oppenheimer
VIDEO/EXTVID Relay
65c22
65c51
FTDI/USB Adapter
Jumper Settings
Decode Logic
Expantion Port 1
Expantion Port 2
Expantion Port 4
Expantion Port 3
I/O Port
CPU
Jumper Setting
AT28C256/27128
Jumper Debug Settings
Pin 4 Is The Signal.
Had to use PB7 :O

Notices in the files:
parts and their libraries:
SparkFun-Switches: Licensing: Creative Commons ShareAlike 4.0 International - https://creativecommons.org/licenses/by-sa/4.0
